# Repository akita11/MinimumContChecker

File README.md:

# Minimim Cont Checker

# 使い方

LR41ボタン電池を2個、このように入れます（向きに注意してください）。

上部の電源スイッチを押すと緑LEDが点灯します。

2本のテスターリードをチェック箇所にあて、2点が短絡（およそ1Ω以下）していると、ブザーが鳴り、黄LEDが点灯します。

使用後は電源スイッチをもう一度押してオフにしておいてください。

※2個の電池の電圧の合計が2V程度になるまで使えます。

## Author

Junichi Akita (akita@ifdl.jp, @akita11)

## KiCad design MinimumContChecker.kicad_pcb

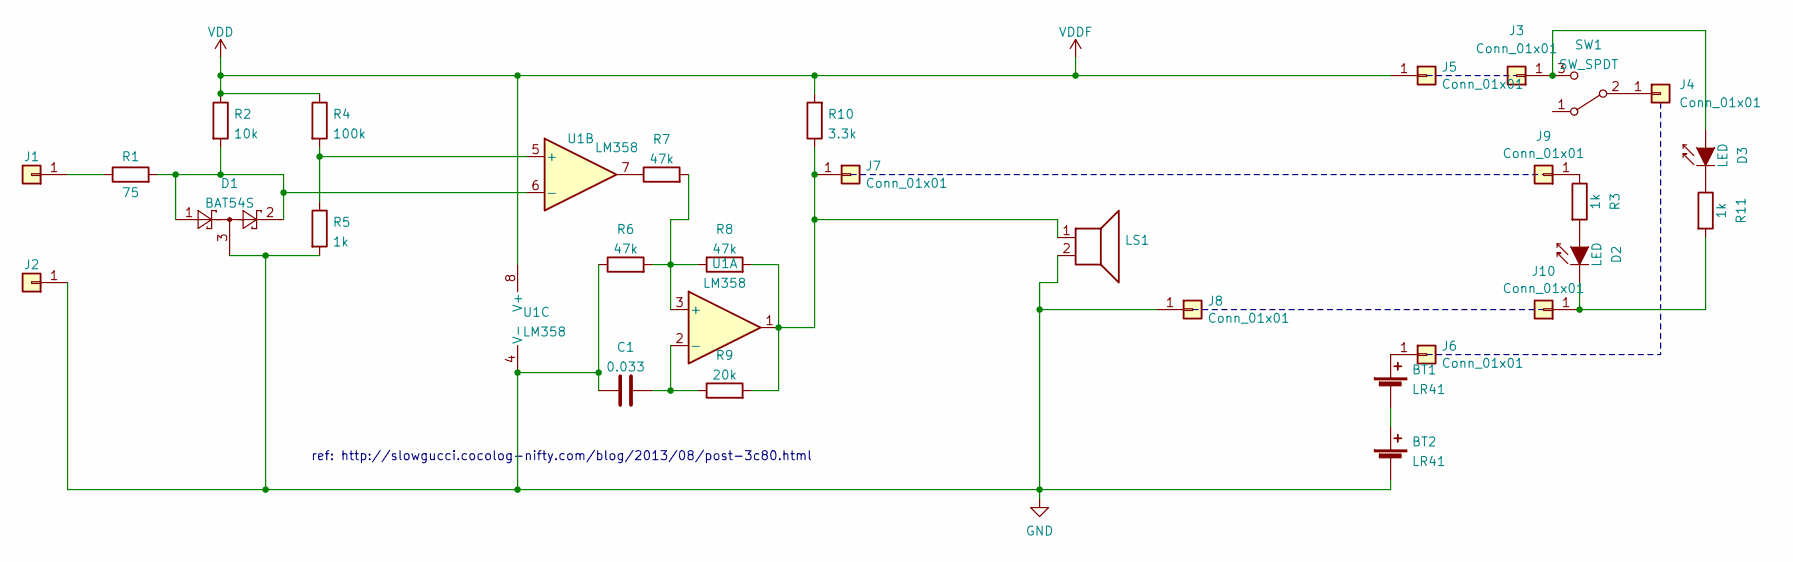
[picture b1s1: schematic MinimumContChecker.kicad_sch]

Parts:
BT1, BT2: LR41; BAT_LR41
C1: 0.033; C_0603_1608Metric
D1: BAT54S; SOT-23
D2, D3: LED; LED_0603_1608Metric
J1, J2: Conn_01x01; Pad_SMD1.6x3.2mm
J3, J4, J5, J6, J7, J8, J9, J10: Conn_01x01; Pad_SMD1.6mm
LS1: Speaker; BZ_9mmSQ
R1: 75; R_0603_1608Metric
R2: 10k; R_0603_1608Metric
R3, R5, R11: 1k; R_0603_1608Metric
R4: 100k; R_0603_1608Metric
R6, R7, R8: 47k; R_0603_1608Metric
R9: 20k; R_0603_1608Metric
R10: 3.3k; R_0603_1608Metric
SW1: SW_SPDT; SW_B22E60
U1: LM358; TSSOP-8_3x3mm_P0.65mm

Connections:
GND: BT2.2 (-), C1.1, D1.3, J2.1, J8.1, LS1.2, R5.2, R6.1, U1.4 (V-)
unnamed: BT1.1 (+), J6.1
unnamed: BT1.2 (-), BT2.1 (+)
unnamed: D2.2 (A), R3.2
unnamed: D2.1 (K), J10.1, R11.2
unnamed: D3.2 (A), J3.1, SW1.3 (C)
unnamed: D3.1 (K), R11.1
unnamed: J1.1, R1.1
unnamed: J4.1, SW1.2 (B)
unnamed: J7.1, LS1.1, R8.2, R9.2, R10.1, U1.1
unnamed: J9.1, R3.1
unnamed: R7.1, U1.7
unnamed: R6.2, R7.2, R8.1, U1.3 (+)
unnamed: C1.2, R9.1, U1.2 (-)
unnamed: R4.2, R5.1, U1.5 (+)
unnamed: D1.1, D1.2, R1.2, R2.2, U1.6 (-)
VDD: J5.1, R2.1, R4.1, R10.2, U1.8 (V+)

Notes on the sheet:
ref: http://slowgucci.cocolog-nifty.com/blog/2013/08/post-3c80.html

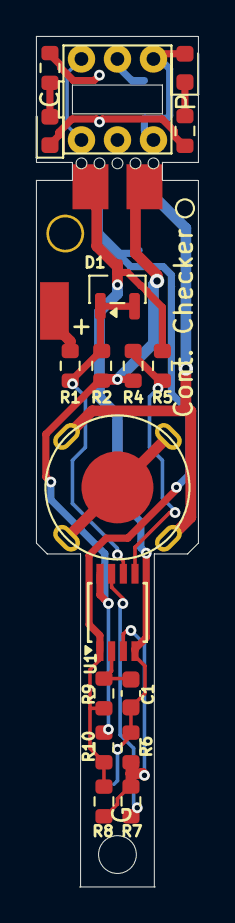
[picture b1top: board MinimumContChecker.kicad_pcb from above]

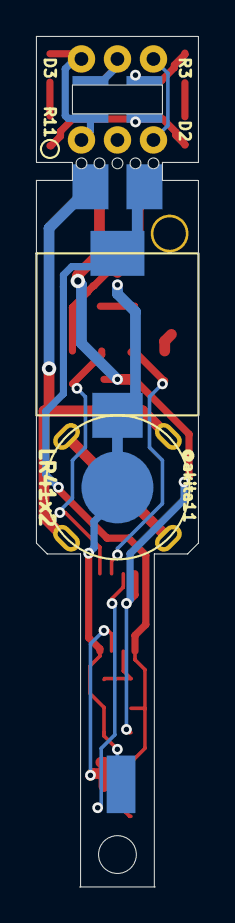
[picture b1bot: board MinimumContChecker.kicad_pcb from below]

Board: 2 copper layers, 9.0 x 47.2 mm, 30 parts (9 on the bottom side), 17 nets.
